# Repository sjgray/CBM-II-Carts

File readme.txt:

CBM-II Cartridges - Steve J. Gray
=================

This repository will contain CBM-II cartridges of my own design plus (in the future)
clones of original cartridges.

Normal cartridges space is in BANK 15, with 3 decoded ranges:

* $2000-3FFF (8K)
* $4000-5FFF (8K)
* $6000-7FFF (8K)

There are also 2 additional areas that are decoded but not available on the cartridge port.
These can be used by connecting wires from the cartridge to pins on a PLA chip inside the computer.
The areas are:

* $1000-1FFF (4K) - B and P-series
* $C000-CFFF (4K) - Not available on P-series!

Directory   Ver  Date      Status    Description
---------   ---  ----      ------    -----------
ROMCart     1.0  20240412  Working   My 256K ROM-only cart. 8 sets of 32K ($2000-$7FFF, plus one definable)
RAM+ROMCart 1.0  20250502  Working   My 32K RAM/256K ROM cart. RAM: (24K+8K), ROM: 8 sets of 32K ($2000-$7FFF, plus one definable)
CartImages   -   20250425  -         Collections of 256K ROM cartridge sets

Webpage: cbmsteve.ca/cbm2cart/index.html

Steve

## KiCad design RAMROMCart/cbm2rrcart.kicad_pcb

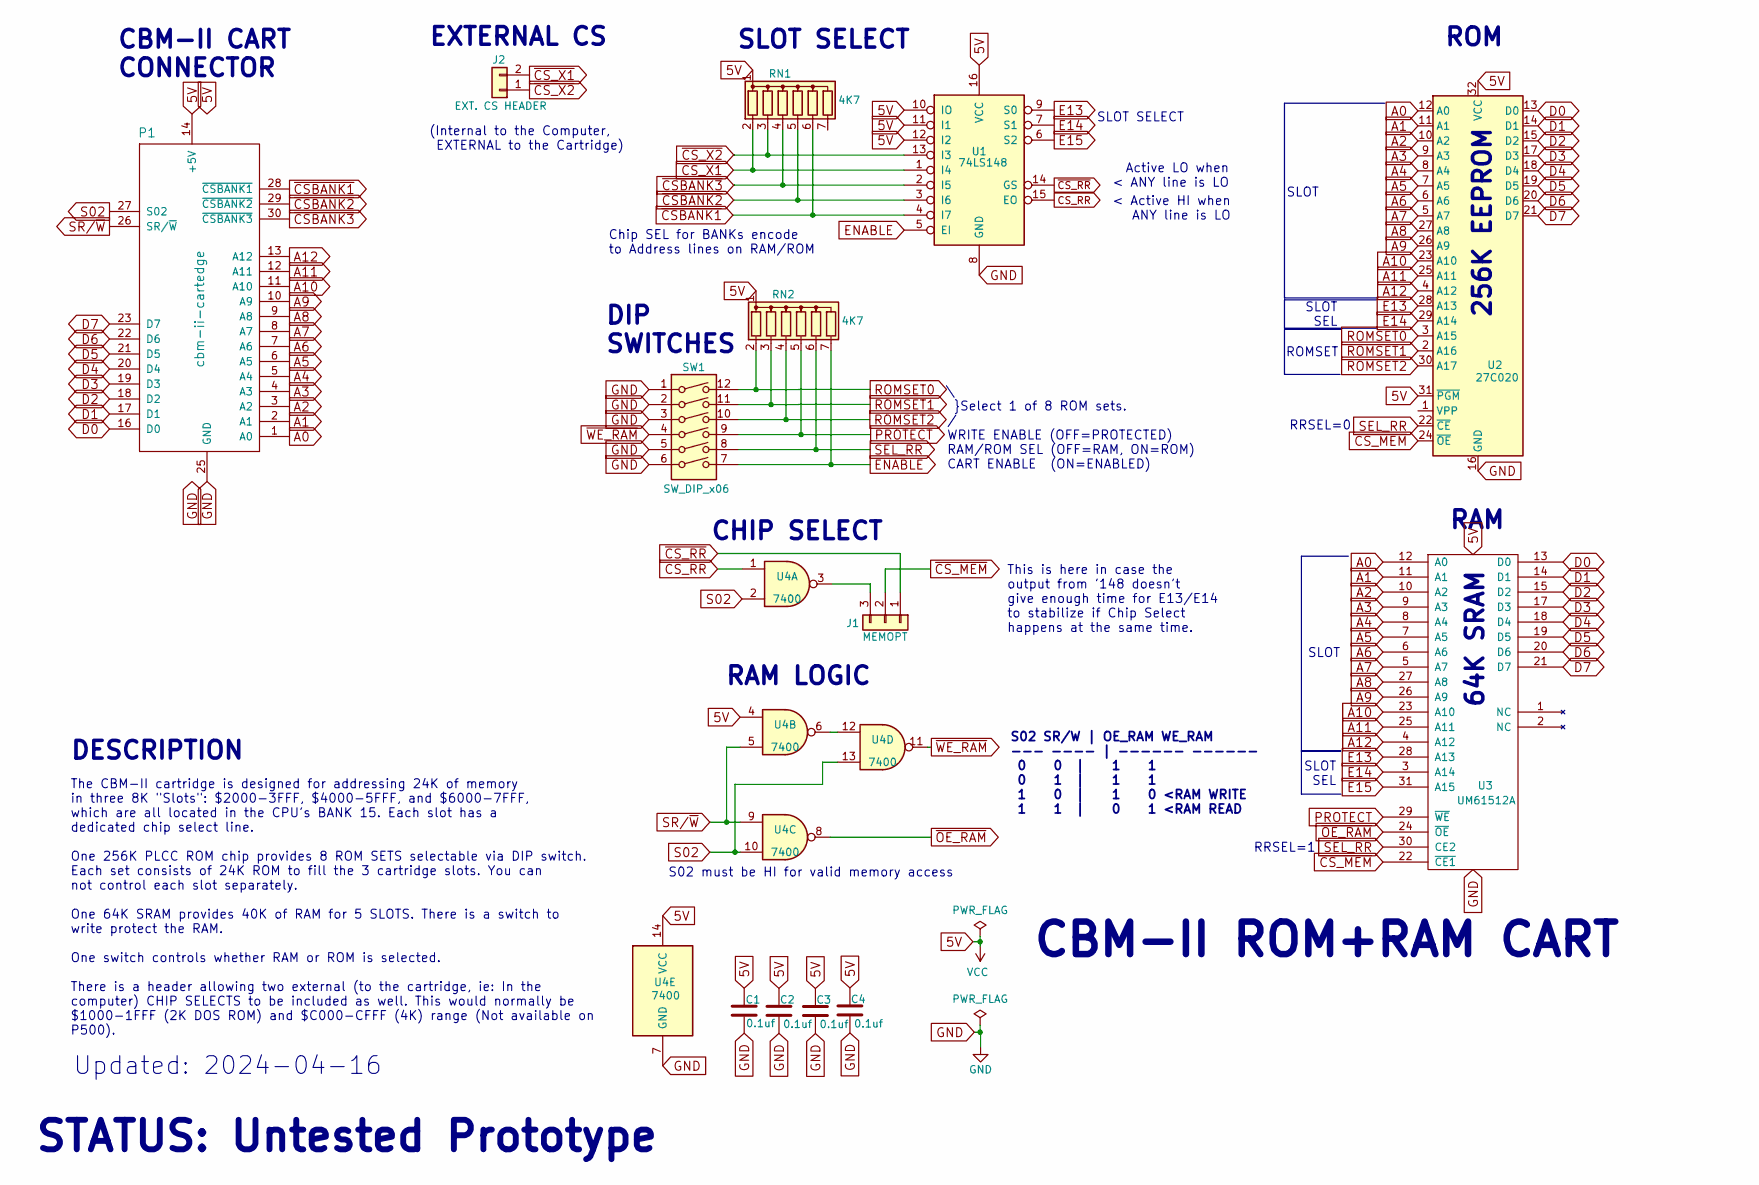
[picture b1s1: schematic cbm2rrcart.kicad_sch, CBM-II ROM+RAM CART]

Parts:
C1: 0.1uf; PinHeader_1x03_P2.54mm_Vertical_SMD_Pin1Right
C2, C3, C4: 0.1uf; C_Disc_D3.4mm_W2.1mm_P2.50mm
J1: MEMOPT; PinHeader_1x03_P2.54mm_Vertical
J2: EXT. CS HEADER; PinHeader_1x02_P2.54mm_Vertical
P1: cbm-ii-cartedge; CBM2-Cart-Edge
RN1, RN2: 4K7; R_Array_SIP7
SW1: SW_DIP_x06; SW_DIP_SPSTx06_Piano_10.8x16.8mm_W7.62mm_P2.54mm
U1: 74LS148; DIP-16_W7.62mm_LongPads
U2: 27C020; DIP-32_W15.24mm_LongPads
U3: UM61512A; DIP-32_W7.62mm
U4: 7400; DIP-14_W7.62mm_LongPads

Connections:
5V: C1.1, C2.1, C3.1, C4.1, P1.14 (+5V), P1.15 (+5V), RN1.1 (common), RN2.1 (common), U1.10 (IO), U1.11 (I1), U1.12 (I2), U1.16 (VCC), U2.31 (~PGM), U2.32 (VCC), U3.32 (VCC), U4.4, U4.14 (VCC)
A0: P1.1 (A0), U2.12 (A0), U3.12 (A0)
A1: P1.2 (A1), U2.11 (A1), U3.11 (A1)
A2: P1.3 (A2), U2.10 (A2), U3.10 (A2)
A3: P1.4 (A3), U2.9 (A3), U3.9 (A3)
A4: P1.5 (A4), U2.8 (A4), U3.8 (A4)
A5: P1.6 (A5), U2.7 (A5), U3.7 (A5)
A6: P1.7 (A6), U2.6 (A6), U3.6 (A6)
A7: P1.8 (A7), U2.5 (A7), U3.5 (A7)
A8: P1.9 (A8), U2.27 (A8), U3.27 (A8)
A9: P1.10 (A9), U2.26 (A9), U3.26 (A9)
A10: P1.11 (A10), U2.23 (A10), U3.23 (A10)
A11: P1.12 (A11), U2.25 (A11), U3.25 (A11)
A12: P1.13 (A12), U2.4 (A12), U3.4 (A12)
CS_RR: U1.15 (EO), U4.1
D0: P1.16 (D0), U2.13 (D0), U3.13 (D0)
D1: P1.17 (D1), U2.14 (D1), U3.14 (D1)
D2: P1.18 (D2), U2.15 (D2), U3.15 (D2)
D3: P1.19 (D3), U2.17 (D3), U3.17 (D3)
D4: P1.20 (D4), U2.18 (D4), U3.18 (D4)
D5: P1.21 (D5), U2.19 (D5), U3.19 (D5)
D6: P1.22 (D6), U2.20 (D6), U3.20 (D6)
D7: P1.23 (D7), U2.21 (D7), U3.21 (D7)
E13: U1.9 (S0), U2.28 (A13), U3.28 (A13)
E14: U1.7 (S1), U2.29 (A14), U3.3 (A14)
E15: U1.6 (S2), U3.31 (A15)
ENABLE: RN2.7 (R6), SW1.7, U1.5 (EI)
GND: C1.2, C2.2, C3.2, C4.2, P1.24 (GND), P1.25 (GND), SW1.1, SW1.2, SW1.3, SW1.5, SW1.6, U1.8 (GND), U2.16 (GND), U3.16 (GND), U4.7 (GND)
unnamed: J1.3, U4.3
unnamed: U4.6, U4.12
PROTECT: RN2.5 (R4), SW1.9, U3.29 (~WE)
ROMSET0: RN2.2 (R1), SW1.12, U2.3 (A15)
ROMSET1: RN2.3 (R2), SW1.11, U2.2 (A16)
ROMSET2: RN2.4 (R3), SW1.10, U2.30 (A17)
S02: P1.27 (S02), U4.2, U4.10, U4.13
SEL_RR: RN2.6 (R5), SW1.8, U2.22 (~CE), U3.30 (CE2)
SR/~W: P1.26 (SR/~W), U4.5, U4.9
~CSBANK1: P1.28 (~CSBANK1), RN1.6 (R5), U1.4 (I7)
~CSBANK2: P1.29 (~CSBANK2), RN1.5 (R4), U1.3 (I6)
~CSBANK3: P1.30 (~CSBANK3), RN1.4 (R3), U1.2 (I5)
~CS_MEM: J1.2, U2.24 (~OE), U3.22 (~CE1)
~CS_RR: J1.1, U1.14 (GS)
~CS_X1: J2.2, RN1.2 (R1), U1.1 (I4)
~CS_X2: J2.1, RN1.3 (R2), U1.13 (I3)
~OE_RAM: U3.24 (~OE), U4.8
~WE_RAM: SW1.4, U4.11

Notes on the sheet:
DESCRIPTION
CBM-II CART CONNECTOR
S02 must be HI for valid memory access
SLOT SELECT
SLOT SEL
RAM LOGIC
SLOT
ROM
The CBM-II cartridge is designed for addressing 24K of memory in three 8K "Slots": $2000-3FFF, $4000-5FFF, and $6000-7FFF, which are all located in the CPU's BANK 15. Each slot has a dedicated chip select line. One 256K PLCC ROM chip provides 8 ROM SETS selectable via DIP switch. Each set consists 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
RRSEL=0
Active LO when < ANY line is LO
DIP SWITCHES
Updated: 2024-04-16
64K SRAM
CBM-II ROM+RAM CART
RRSEL=1
This is here in case the output from '148 doesn't give enough time for E13/E14 to stabilize if Chip Select happens at the same time.
S02 SR/W | OE_RAM WE_RAM --- ---- | ------ ------ 0 0 | 1 1 0 1 | 1 1 1 0 | 1 0 <RAM WRITE 1 1 | 0 1 <RAM READ
ROMSET
256K EEPROM
STATUS: Untested Prototype
\ }Select 1 of 8 ROM sets. / WRITE ENABLE (OFF=PROTECTED) RAM/ROM SEL (OFF=RAM, ON=ROM) CART ENABLE (ON=ENABLED)
(Internal to the Computer, EXTERNAL to the Cartridge)
EXTERNAL CS
< Active HI when ANY line is LO
CHIP SELECT
RAM
Chip SEL for BANKs encode to Address lines on RAM/ROM

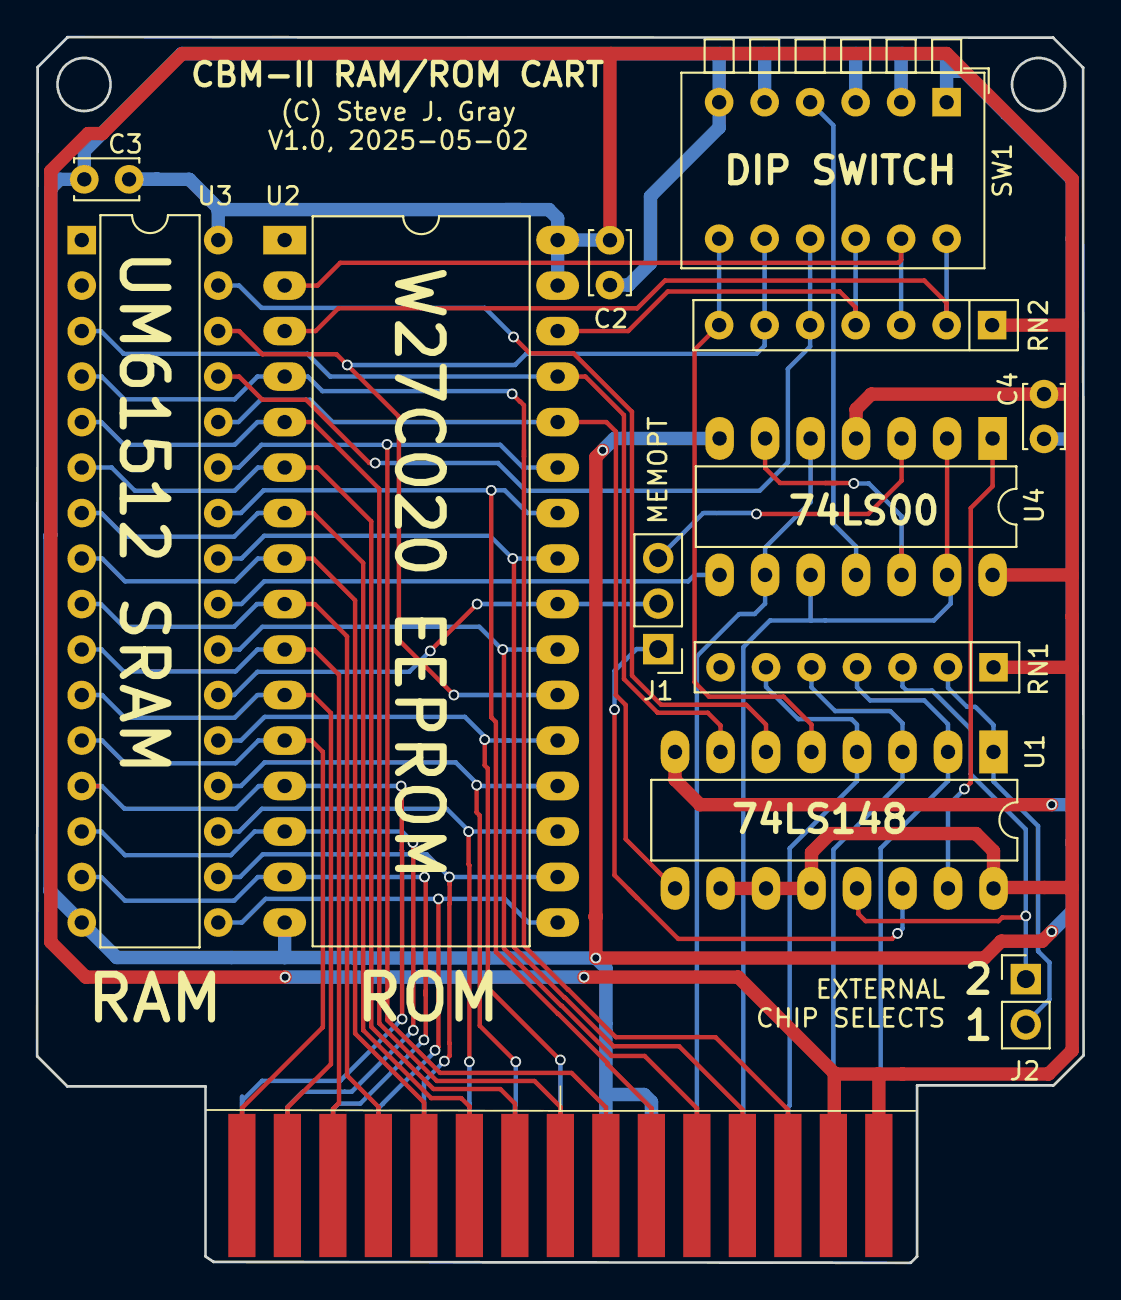
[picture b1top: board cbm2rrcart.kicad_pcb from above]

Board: 2 copper layers, 58.4 x 68.4 mm, 13 parts (0 on the bottom side), 46 nets.

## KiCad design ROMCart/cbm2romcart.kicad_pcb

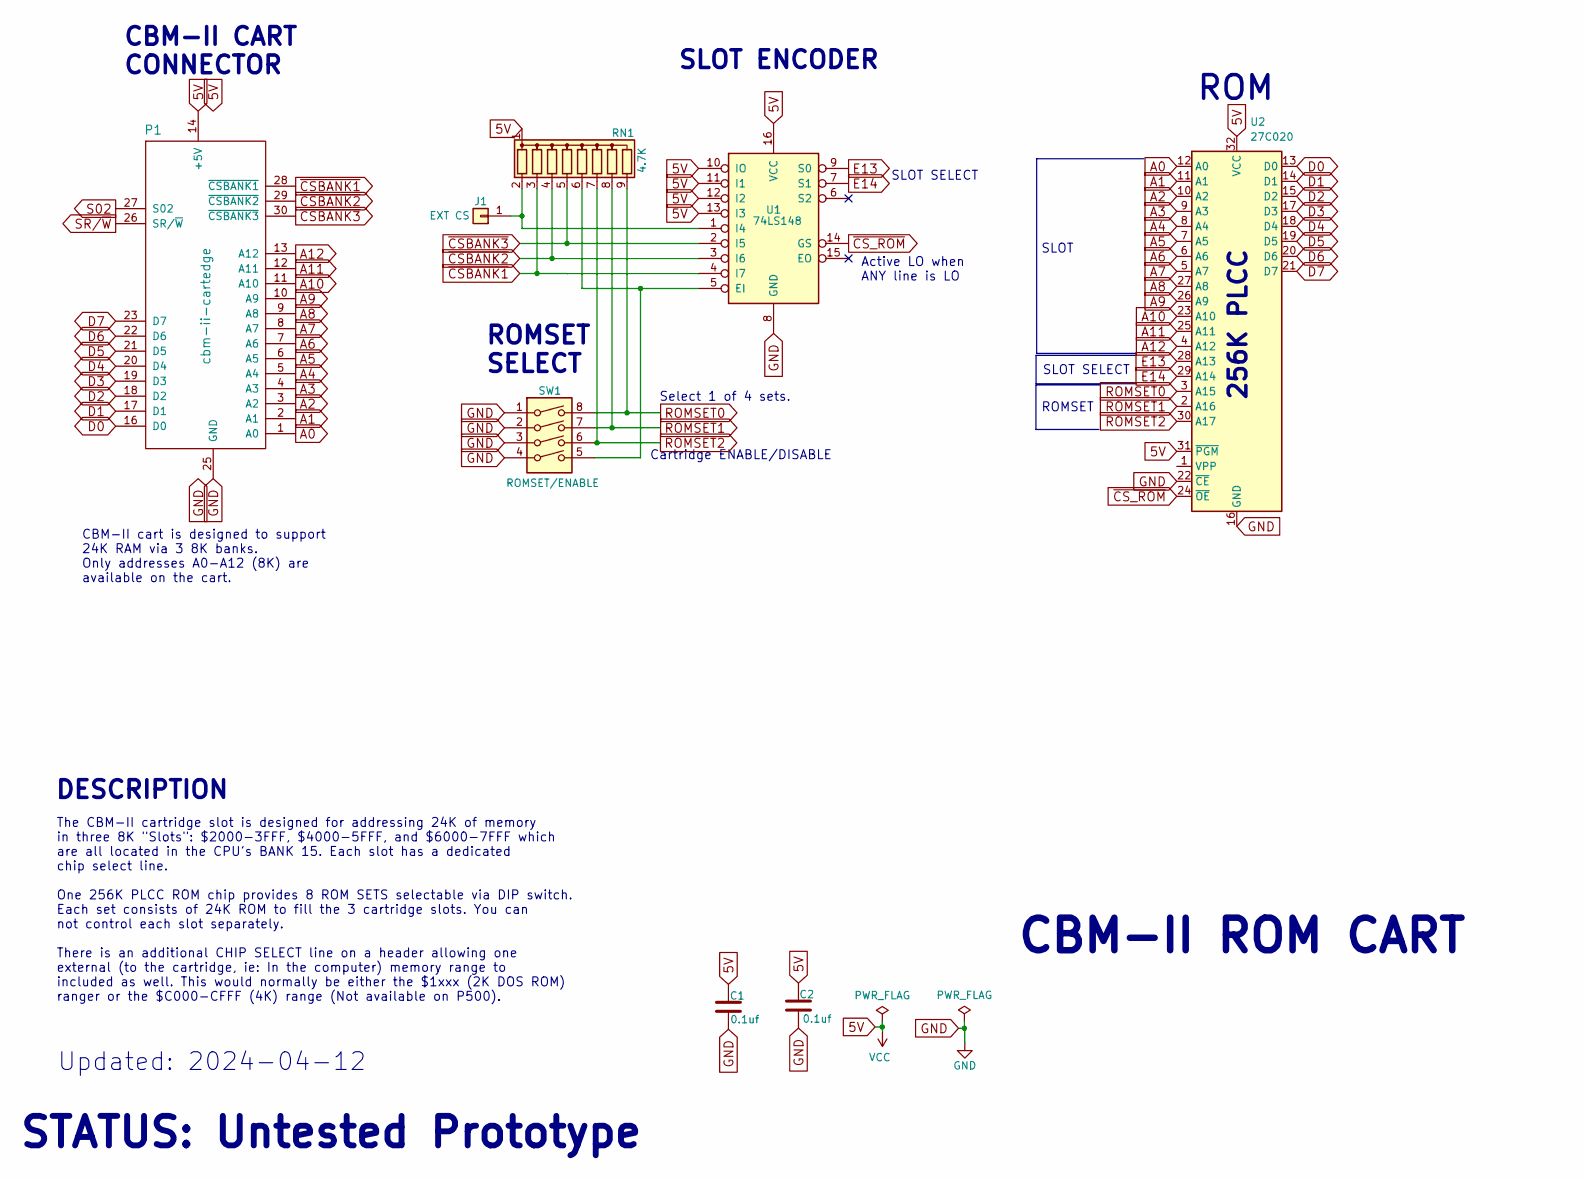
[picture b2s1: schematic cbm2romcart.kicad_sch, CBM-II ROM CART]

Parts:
C1, C2: 0.1uf; C_Disc_D3.4mm_W2.1mm_P2.50mm
J1: EXT CS; PinHeader_1x01_P2.54mm_Vertical
P1: cbm-ii-cartedge; CBM2-Cart-Edge
RN1: 4.7K; R_Array_SIP9
SW1: ROMSET/ENABLE; SW_DIP_SPSTx04_Piano_10.8x11.72mm_W7.62mm_P2.54mm
U1: 74LS148; DIP-16_W7.62mm_LongPads
U2: 27C020; PLCC-32_THT-Socket

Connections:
5V: C1.1, C2.1, P1.14 (+5V), P1.15 (+5V), RN1.1 (common), U1.10 (IO), U1.11 (I1), U1.12 (I2), U1.13 (I3), U1.16 (VCC), U2.31 (~PGM), U2.32 (VCC)
A0: P1.1 (A0), U2.12 (A0)
A1: P1.2 (A1), U2.11 (A1)
A2: P1.3 (A2), U2.10 (A2)
A3: P1.4 (A3), U2.9 (A3)
A4: P1.5 (A4), U2.8 (A4)
A5: P1.6 (A5), U2.7 (A5)
A6: P1.7 (A6), U2.6 (A6)
A7: P1.8 (A7), U2.5 (A7)
A8: P1.9 (A8), U2.27 (A8)
A9: P1.10 (A9), U2.26 (A9)
A10: P1.11 (A10), U2.23 (A10)
A11: P1.12 (A11), U2.25 (A11)
A12: P1.13 (A12), U2.4 (A12)
D0: P1.16 (D0), U2.13 (D0)
D1: P1.17 (D1), U2.14 (D1)
D2: P1.18 (D2), U2.15 (D2)
D3: P1.19 (D3), U2.17 (D3)
D4: P1.20 (D4), U2.18 (D4)
D5: P1.21 (D5), U2.19 (D5)
D6: P1.22 (D6), U2.20 (D6)
D7: P1.23 (D7), U2.21 (D7)
E13: U1.9 (S0), U2.28 (A13)
E14: U1.7 (S1), U2.29 (A14)
GND: C1.2, C2.2, P1.24 (GND), P1.25 (GND), SW1.1, SW1.2, SW1.3, SW1.4, U1.8 (GND), U2.16 (GND), U2.22 (~CE)
unnamed: J1.1, RN1.2 (R1), U1.1 (I4)
unnamed: RN1.6 (R5), SW1.5, U1.5 (EI)
ROMSET0: RN1.9 (R8), SW1.8, U2.3 (A15)
ROMSET1: RN1.8 (R7), SW1.7, U2.2 (A16)
ROMSET2: RN1.7 (R6), SW1.6, U2.30 (A17)
S02: P1.27 (S02)
SR/~W: P1.26 (SR/~W)
~CSBANK1: P1.28 (~CSBANK1), RN1.3 (R2), U1.4 (I7)
~CSBANK2: P1.29 (~CSBANK2), RN1.4 (R3), U1.3 (I6)
~CSBANK3: P1.30 (~CSBANK3), RN1.5 (R4), U1.2 (I5)
~CS_ROM: U1.14 (GS), U2.24 (~OE)

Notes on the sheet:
Select 1 of 4 sets.
DESCRIPTION
CBM-II CART CONNECTOR
ROM
SLOT ENCODER
SLOT SELECT
SLOT
The CBM-II cartridge slot is designed for addressing 24K of memory in three 8K "Slots": $2000-3FFF, $4000-5FFF, and $6000-7FFF which are all located in the CPU's BANK 15. Each slot has a dedicated chip select line. One 256K PLCC ROM chip provides 8 ROM SETS selectable via DIP switch. Each set consi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
CBM-II cart is designed to support 24K RAM via 3 8K banks. Only addresses A0-A12 (8K) are available on the cart.
Active LO when ANY line is LO
ROMSET SELECT
Updated: 2024-04-12
CBM-II ROM CART
Cartridge ENABLE/DISABLE
ROMSET
256K PLCC
STATUS: Untested Prototype

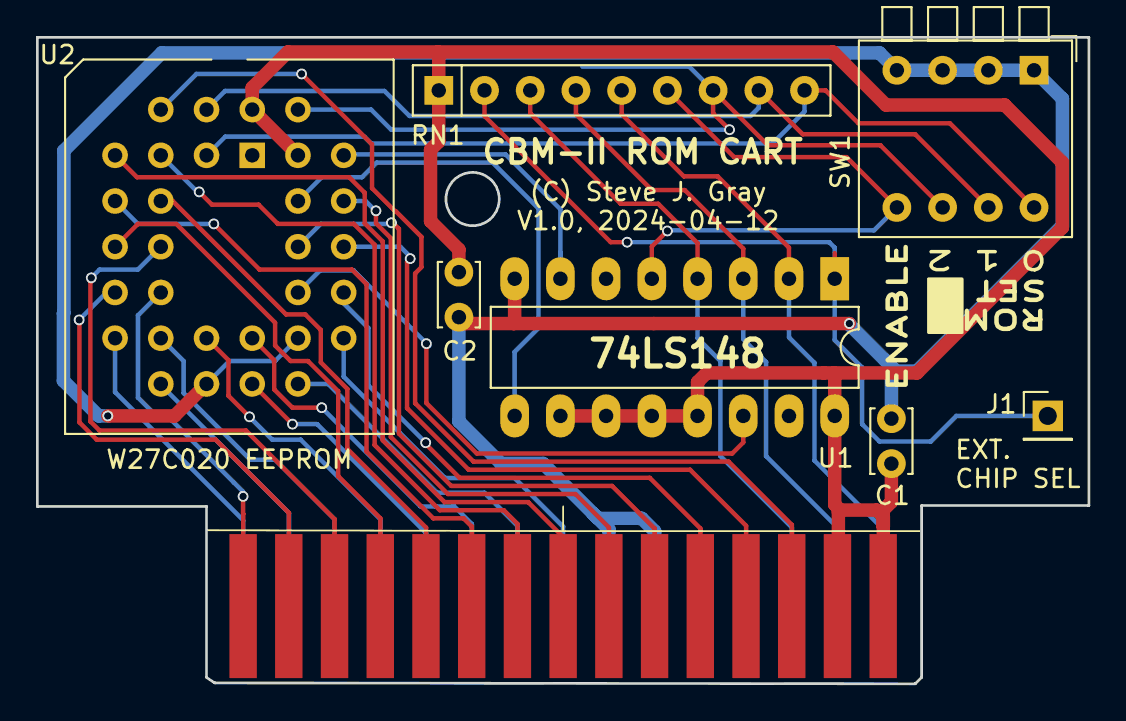
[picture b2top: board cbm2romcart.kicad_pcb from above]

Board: 2 copper layers, 58.4 x 35.9 mm, 8 parts (0 on the bottom side), 34 nets.

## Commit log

2025-04-06 Initial
    Add my 256K ROM-only cartridge. Allows up to 8 sets of 32K. The regular cartridge slots $2000, $4000, and $6000 (8K each) become one 24K "set", plus you can add another 8K slot using the External Chi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
2025-04-06 Fix PDF
    The PDF schematic was incorrect. Fixed!
2025-04-25 Add first ROM SET
    Includes PET Emulator (pre-release), Diagnostics, Calc Result, IEC, Monitor 610.
2025-05-15 Add RAM-ROM Cart V1.0
    The RAM/ROM cart adds 24K of RAM in the cartridge space plus up to 8K in the external space ($1000-1FFF or $C000-CFFF) or up to 8 selectable sets of 24K of ROM plus 4K of external space. The RAM can 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
2025-05-16 Move Cartridge Images to main folder
    Cartridge Sets will work on the ROMCart or the RAM/ROMCart.
2025-05-20 Update PDF
    Update status to "working". Fix some description text.
2025-07-18 Add 256K Cart Set#2
    Updated PET Emulator. Add Michau's 8088 card boot ROM
